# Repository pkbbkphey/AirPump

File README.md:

# AirPump

# Tools
- [Chinese to GBK](https://www.tusucao.com/commons/gbk/)

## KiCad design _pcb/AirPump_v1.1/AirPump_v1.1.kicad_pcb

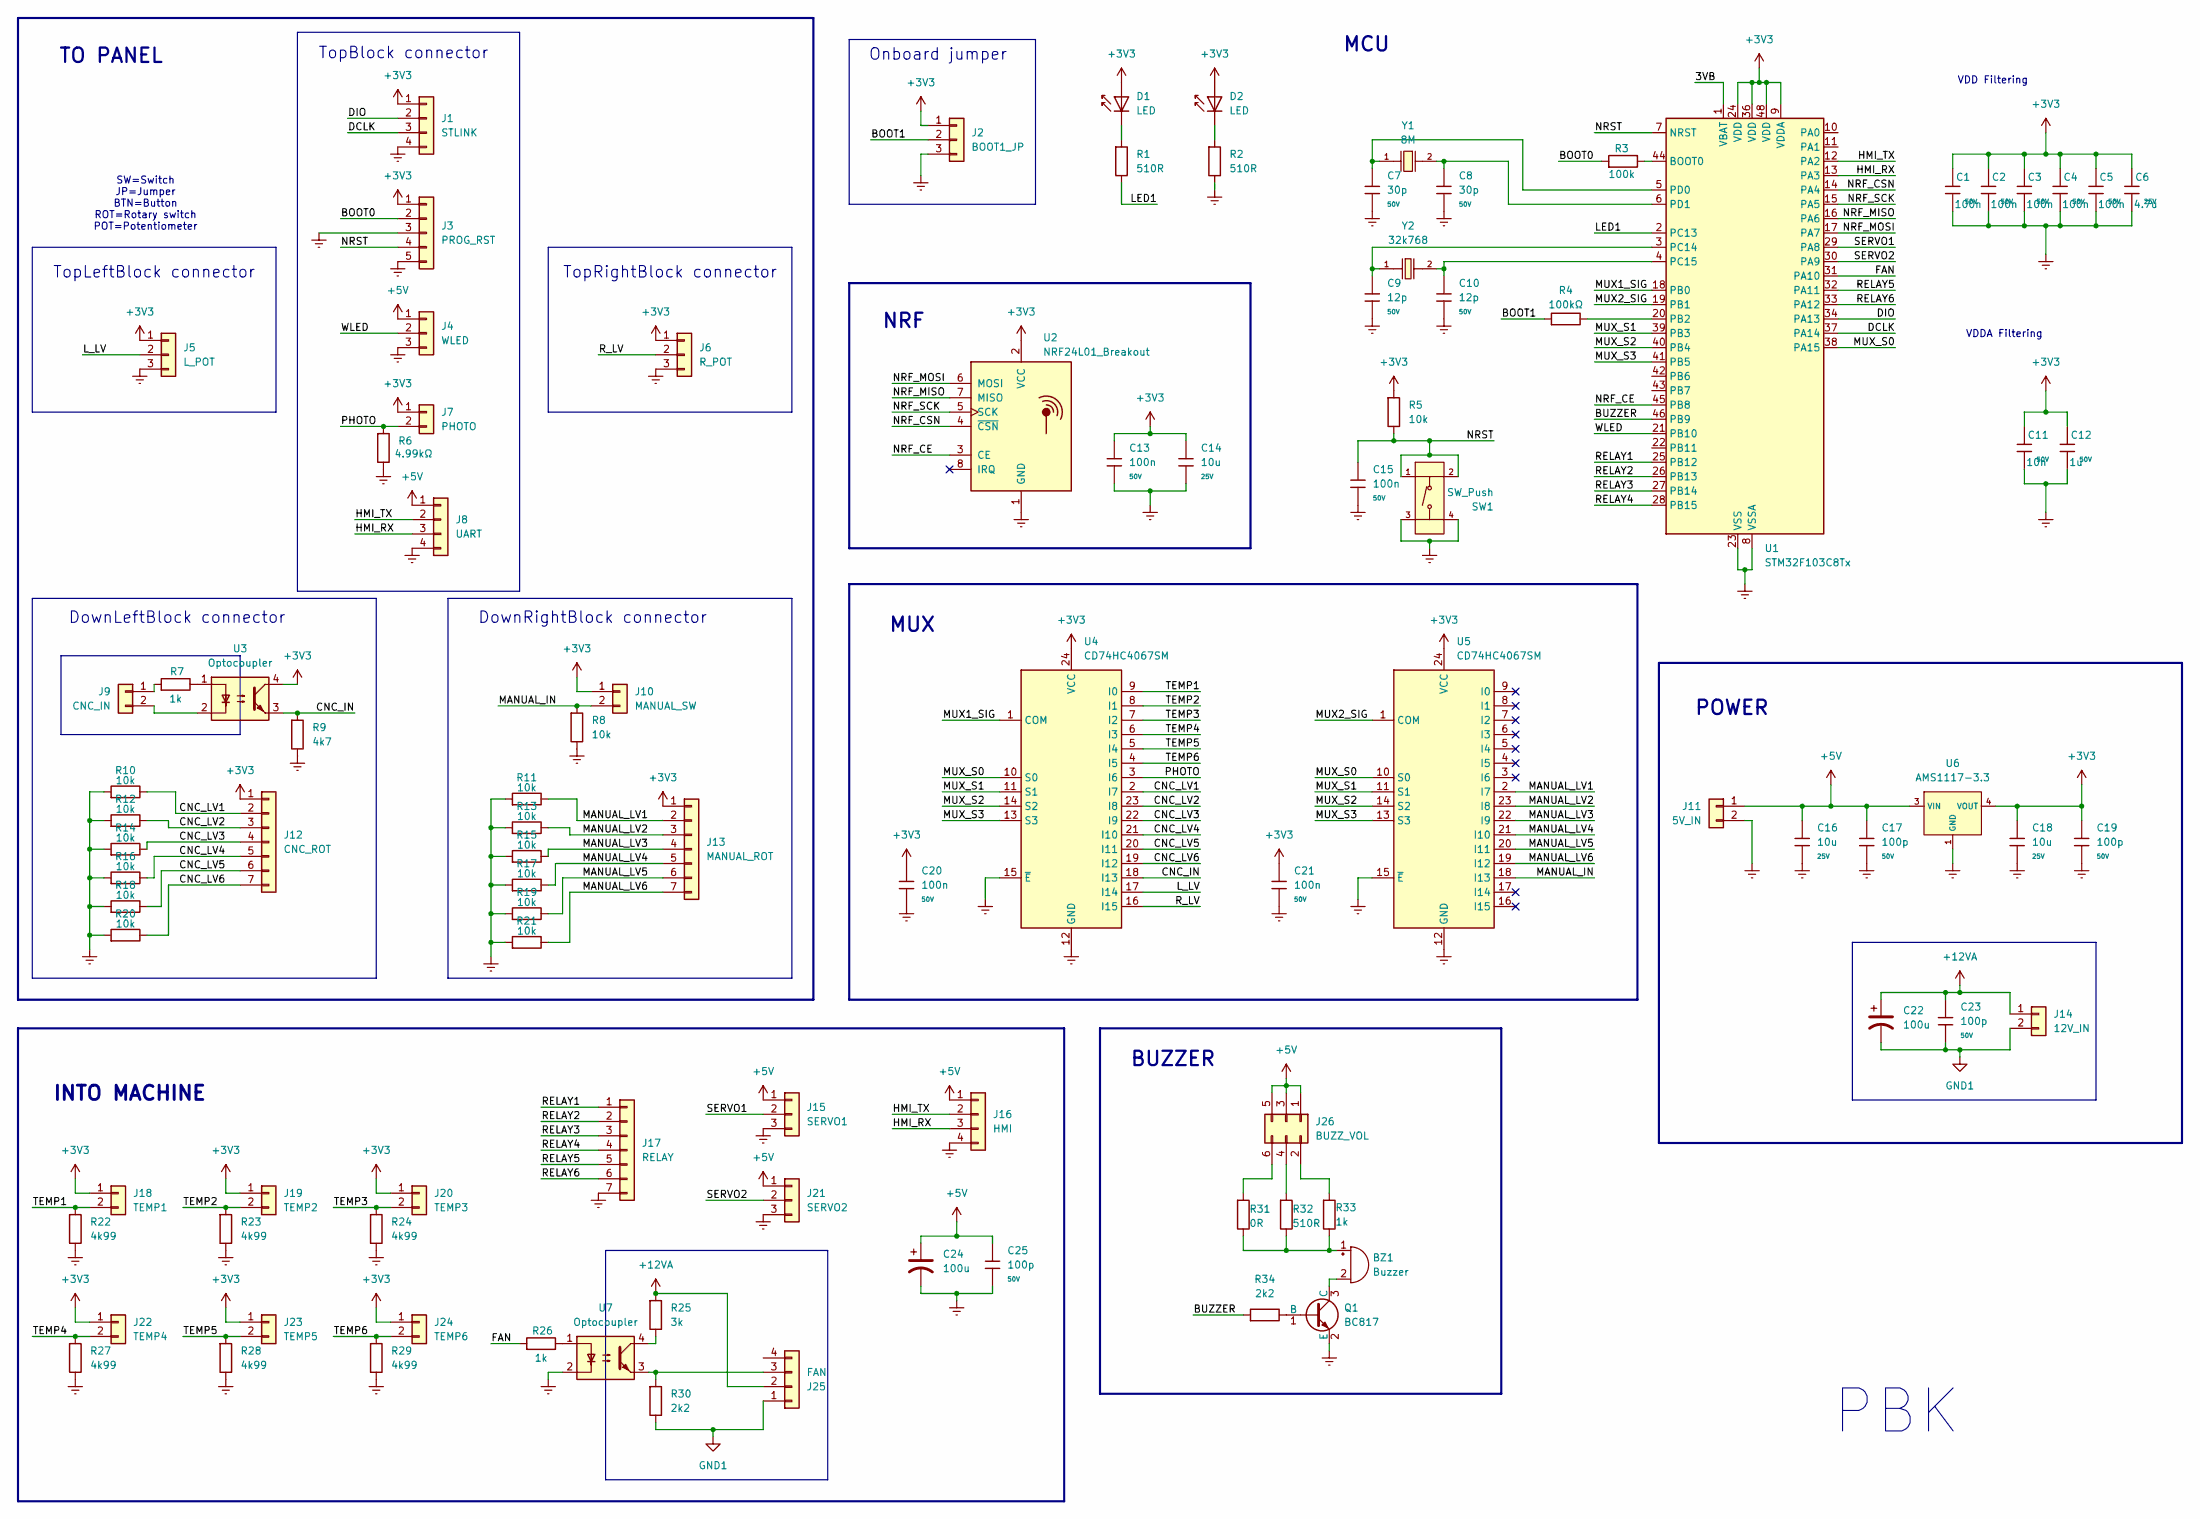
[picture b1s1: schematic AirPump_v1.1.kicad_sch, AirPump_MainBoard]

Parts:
BZ1: Buzzer; MagneticBuzzer_StarMicronics_QMX
C1, C2, C3, C4, C5, C13, C15, C20, C21: 100n; C_0603; Voltage Rated 50V; Tolerance ±10%; Part CC0603KRX7R9BB104; LCSC C14663
C6: 4.7u; C_0805; Voltage Rated 25V; Tolerance ±10%; Part CL21A475KAQNNNE; LCSC C1779
C7, C8: 30p; C_0603; Voltage Rated 50V; Tolerance ±5%; Part 0603CG300J500NT; LCSC C1658
C9, C10: 12p; C_0603; Voltage Rated 50V; Tolerance ±5%; Part CL10C120JB8NNNC; LCSC C38523
C11: 10n; C_0603; Voltage Rated 50V; Tolerance ±10%; Part 0603B103K500NT; LCSC C57112
C12: 1u; C_0603; Voltage Rated 50V; Tolerance ±10%; Part CL10A105KB8NNNC; LCSC C15849
C14, C16, C18: 10u; C_0805; Voltage Rated 25V; Tolerance ±10%; Part CL21A106KAYNNNE; LCSC C15850
C17, C19, C23, C25: 100p; C_0603; Voltage Rated 50V; Tolerance ±5%; Part CL10C101JB8NNNC; LCSC C14858
C22, C24: 100u; CP_Elec_6.3x5.4
D1: LED; D_0603; Part KT-0603W; LCSC C2290
D2: LED; D_0603; Part KT-0603R; LCSC C2286
J1: STLINK; JST_PH_B4B-PH-K_1x04_P2.00mm_Vertical
J2: BOOT1_JP; PinHeader_1x03_P2.54mm_Vertical
J3: PROG_RST; JST_PH_B5B-PH-K_1x05_P2.00mm_Vertical
J4: WLED; Molex_KK-254_AE-6410-03A_1x03_P2.54mm_Vertical
J5: L_POT; JST_PH_B3B-PH-K_1x03_P2.00mm_Vertical
J6: R_POT; JST_PH_B3B-PH-K_1x03_P2.00mm_Vertical
J7: PHOTO; JST_PH_B2B-PH-K_1x02_P2.00mm_Vertical
J8: UART; JST_PH_B4B-PH-K_1x04_P2.00mm_Vertical
J9: CNC_IN; JST_PH_B2B-PH-K_1x02_P2.00mm_Vertical
J10: MANUAL_SW; JST_PH_B2B-PH-K_1x02_P2.00mm_Vertical
J11: 5V_IN; Molex_KK-254_AE-6410-02A_1x02_P2.54mm_Vertical
J12: CNC_ROT; JST_PH_B7B-PH-K_1x07_P2.00mm_Vertical
J13: MANUAL_ROT; JST_PH_B7B-PH-K_1x07_P2.00mm_Vertical
J14: 12V_IN; Molex_KK-254_AE-6410-02A_1x02_P2.54mm_Vertical
J15: SERVO1; Molex_KK-254_AE-6410-03A_1x03_P2.54mm_Vertical
J16: HMI; Molex_KK-254_AE-6410-04A_1x04_P2.54mm_Vertical
J17: RELAY; JST_PH_B7B-PH-K_1x07_P2.00mm_Vertical
J18: TEMP1; JST_PH_B2B-PH-K_1x02_P2.00mm_Vertical
J19: TEMP2; JST_PH_B2B-PH-K_1x02_P2.00mm_Vertical
J20: TEMP3; JST_PH_B2B-PH-K_1x02_P2.00mm_Vertical
J21: SERVO2; Molex_KK-254_AE-6410-03A_1x03_P2.54mm_Vertical
J22: TEMP4; JST_PH_B2B-PH-K_1x02_P2.00mm_Vertical
J23: TEMP5; JST_PH_B2B-PH-K_1x02_P2.00mm_Vertical
J24: TEMP6; JST_PH_B2B-PH-K_1x02_P2.00mm_Vertical
J25: FAN; Molex_KK-254_AE-6410-04A_1x04_P2.54mm_Vertical
J26: BUZZ_VOL; PinHeader_2x03_P2.54mm_Vertical
Q1: BC817; Q_SOT-23; Part BC817-25; LCSC C20069154
R1, R2, R32: 510R; R_0603; Overload Voltage (Max) 75V; Tolerance ±1%; Part 0603WAF5100T5E; LCSC C23193
R3, R4: 100k; R_0603; Overload Voltage (Max) 75V; Tolerance ±1%; Part 0603WAF1003T5E; LCSC C25803
R5, R8, R10, R11, R12, R13, R14, R15, R16, R17, R18, R19, R20, R21: 10k; R_0603; Overload Voltage (Max) 75V; Tolerance ±1%; Part 0603WAF1002T5E; LCSC C25804
R6, R22, R23, R24, R27, R28, R29: 4k99; R_0603; Overload Voltage (Max) 75V; Tolerance ±1%; Part 0603WAF4991T5E; LCSC C23046
R7, R26, R33: 1k; R_0603; Overload Voltage (Max) 75V; Tolerance ±1%; Part 0603WAF1001T5E; LCSC C21190
R9: 4k7; R_0603; Overload Voltage (Max) 75V; Tolerance ±1%; Part 0603WAF4701T5E; LCSC C23162
R25: 3k; R_0603; Overload Voltage (Max) 75V; Tolerance ±1%; Part 0603WAF3001T5E; LCSC C4211
R30, R34: 2k2; R_0603; Overload Voltage (Max) 75V; Tolerance ±1%; Part 0603WAF2201T5E; LCSC C4190
R31: 0R; R_0603; Overload Voltage (Max) 75V; Tolerance ±1%; Part 0603WAF0000T5E; LCSC C21189
SW1: SW_Push; SW-SMD_4P-L5.1-W5.1-P3.70-LS6.5-TL-2; Voltage Rating (Dc) 12V; Part TS-1187A-B-A-B; LCSC C318884
U1: STM32F103C8Tx; LQFP-48_7x7mm_P0.5mm; Operating Voltage Range 2V~3.6V; Low Voltage Detection T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 2V~3.6V; Part STM32F103C8T6; LCSC C8734
U2: NRF24L01_Breakout; nRF24L01_Breakout
U3, U7: Optocoupler; SOP-4_3.8x4.1mm_P2.54mm; Part ICPL-356-50CEAXW; LCSC C42432283
U4, U5: CD74HC4067SM; SSOP-24_5.3x8.2mm_P0.65mm
U6: AMS1117-3.3; SOT-223-3_L6.5-W3.4-P2.30-LS7.0-BR; Output Voltage 3.3V; Dropout Voltage 1.3V@(800mA); Part AMS1117-3.3; LCSC C6186
Y1: 8M; CRYSTAL-SMD_L5.0-W3.2; Frequency Tolerance ±10ppm; Part X50328MSB2GI; LCSC C115962
Y2: 32k768; FC-135R_L3.2-W1.5; Frequency Tolerance ±20ppm; Part Q13FC13500004; LCSC C32346

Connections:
+3V3: C1.1, C2.1, C3.1, C4.1, C5.1, C6.1, C11.1, C12.1, C13.1, C14.1, C18.1, C19.1, C20.1, C21.1, D1.2, D2.2, J1.1, J2.1, J3.1, J5.1, J6.1, J7.1, J10.1, J12.1, J13.1, J18.1, J19.1, J20.1, J22.1, J23.1, J24.1, R5.1, U1.9 (VDDA), U1.24 (VDD), U1.36 (VDD), U1.48 (VDD), U2.2 (VCC), U3.4, U4.24 (VCC), U5.24 (VCC), U6.2 (VOUT), U6.4 (VOUT)
+5V: C16.1, C17.1, C24.1, C25.1, J4.1, J8.1, J11.1, J15.1, J16.1, J21.1, J26.1, J26.3, J26.5, U6.3 (VIN)
+12VA: C22.1, C23.1, J14.1, J25.2, R25.1
/3VB: U1.1 (VBAT)
/BOOT0: J3.2, R3.1
/BOOT1: J2.2, R4.1
/BUZZER: R34.1, U1.46 (PB9)
/CNC_IN: R9.1, U3.3, U4.18 (I13)
/CNC_LV1: J12.2, R10.2, U4.2 (I7)
/CNC_LV2: J12.3, R12.2, U4.23 (I8)
/CNC_LV3: J12.4, R14.2, U4.22 (I9)
/CNC_LV4: J12.5, R16.2, U4.21 (I10)
/CNC_LV5: J12.6, R18.2, U4.20 (I11)
/CNC_LV6: J12.7, R20.2, U4.19 (I12)
/DCLK: J1.3, U1.37 (PA14)
/DIO: J1.2, U1.34 (PA13)
/FAN: R26.1, U1.31 (PA10)
/HMI_RX: J8.3, J16.3, U1.13 (PA3)
/HMI_TX: J8.2, J16.2, U1.12 (PA2)
/LED1: R1.2, U1.2 (PC13)
/L_LV: J5.2, U4.17 (I14)
/MANUAL_IN: J10.2, R8.1, U5.18 (I13)
/MANUAL_LV1: J13.2, R11.2, U5.2 (I7)
/MANUAL_LV2: J13.3, R13.2, U5.23 (I8)
/MANUAL_LV3: J13.4, R15.2, U5.22 (I9)
/MANUAL_LV4: J13.5, R17.2, U5.21 (I10)
/MANUAL_LV5: J13.6, R19.2, U5.20 (I11)
/MANUAL_LV6: J13.7, R21.2, U5.19 (I12)
/MUX1_SIG: U1.18 (PB0), U4.1 (COM)
/MUX2_SIG: U1.19 (PB1), U5.1 (COM)
/MUX_S0: U1.38 (PA15), U4.10 (S0), U5.10 (S0)
/MUX_S1: U1.39 (PB3), U4.11 (S1), U5.11 (S1)
/MUX_S2: U1.40 (PB4), U4.14 (S2), U5.14 (S2)
/MUX_S3: U1.41 (PB5), U4.13 (S3), U5.13 (S3)
/NRF_CE: U1.45 (PB8), U2.3 (CE)
/NRF_CSN: U1.14 (PA4), U2.4 (~CSN)
/NRF_MISO: U1.16 (PA6), U2.7 (MISO)
/NRF_MOSI: U1.17 (PA7), U2.6 (MOSI)
/NRF_SCK: U1.15 (PA5), U2.5 (SCK)
/NRST: C15.1, J3.4, R5.2, SW1.1 (A), SW1.2 (B), U1.7 (NRST)
/PHOTO: J7.2, R6.1, U4.3 (I6)
/RELAY1: J17.1, U1.25 (PB12)
/RELAY2: J17.2, U1.26 (PB13)
/RELAY3: J17.3, U1.27 (PB14)
/RELAY4: J17.4, U1.28 (PB15)
/RELAY5: J17.5, U1.32 (PA11)
/RELAY6: J17.6, U1.33 (PA12)
/R_LV: J6.2, U4.16 (I15)
/SERVO1: J15.2, U1.29 (PA8)
/SERVO2: J21.2, U1.30 (PA9)
/TEMP1: J18.2, R22.1, U4.9 (I0)
/TEMP2: J19.2, R23.1, U4.8 (I1)
/TEMP3: J20.2, R24.1, U4.7 (I2)
/TEMP4: J22.2, R27.1, U4.6 (I3)
/TEMP5: J23.2, R28.1, U4.5 (I4)
/TEMP6: J24.2, R29.1, U4.4 (I5)
/WLED: J4.2, U1.21 (PB10)
Earth: C1.2, C2.2, C3.2, C4.2, C5.2, C6.2, C7.2, C8.2, C9.2, C10.2, C11.2, C12.2, C13.2, C14.2, C15.2, C16.2, C17.2, C18.2, C19.2, C20.2, C21.2, C24.2, C25.2, J1.4, J2.3, J3.3, J3.5, J4.3, J5.3, J6.3, J8.4, J11.2, J15.3, J16.4, J17.7, J21.3, Q1.2 (E), R2.2, R6.2, R8.2, R9.2, R10.1, R11.1, R12.1, R13.1, R14.1, R15.1, R16.1, R17.1, R18.1, R19.1, R20.1, R21.1, R22.2, R23.2, R24.2, R27.2, R28.2, R29.2, SW1.3 (C), SW1.4 (D), U1.8 (VSSA), U1.23 (VSS), U1.35 (VSS), U1.47 (VSS), U2.1 (GND), U4.12 (GND), U4.15 (~E), U5.12 (GND), U5.15 (~E), U6.1 (GND), U7.2
GND1: C22.2, C23.2, J14.2, J25.1, R30.2
unnamed: BZ1.1 (+), R31.2, R32.2, R33.2
unnamed: BZ1.2 (-), Q1.3 (C)
unnamed: D1.1, R1.1
unnamed: D2.1, R2.1
unnamed: J9.1, R7.1
unnamed: J9.2, U3.2
unnamed: J25.3, R30.1, U7.3
unnamed: J26.2, R33.1
unnamed: J26.4, R32.1
unnamed: J26.6, R31.1
unnamed: Q1.1 (B), R34.2
unnamed: R7.2, U3.1
unnamed: R25.2, U7.4
unnamed: R26.2, U7.1
unnamed: R3.2, U1.44 (BOOT0)
unnamed: R4.2, U1.20 (PB2)
unnamed: C9.1, U1.3 (PC14), Y2.1
unnamed: C10.1, U1.4 (PC15), Y2.2
unnamed: C7.1, U1.5 (PD0), Y1.1
unnamed: C8.1, U1.6 (PD1), Y1.2

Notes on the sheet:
POWER
DownLeftBlock connector
PBK
VDD Filtering
BUZZER
Onboard jumper
DownRightBlock connector
TopBlock connector
NRF
VDDA Filtering
TopRightBlock connector
TopLeftBlock connector
INTO MACHINE
MUX
TO PANEL
MCU
SW=Switch JP=Jumper BTN=Button ROT=Rotary switch POT=Potentiometer

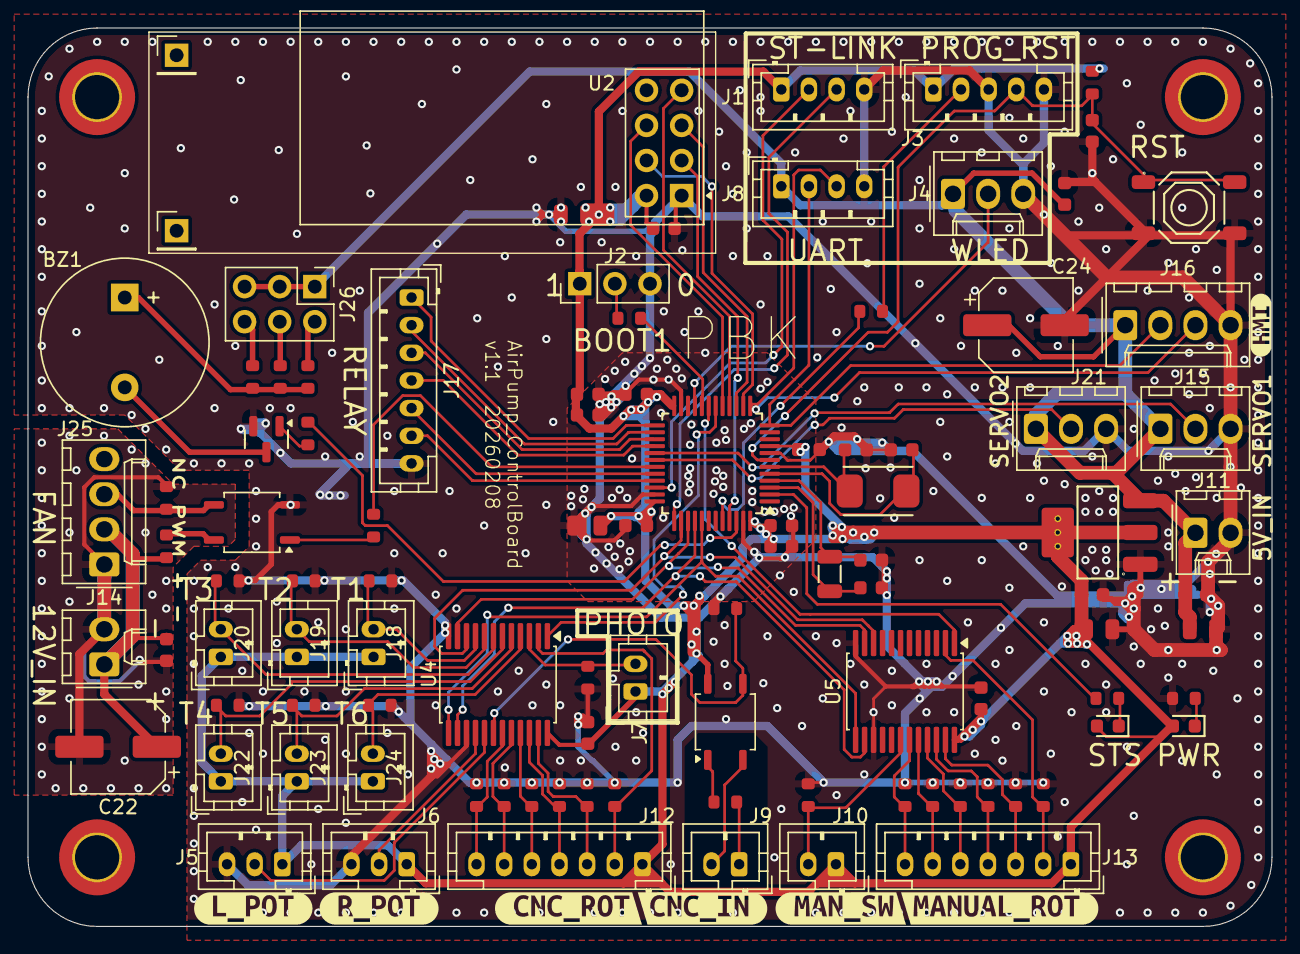
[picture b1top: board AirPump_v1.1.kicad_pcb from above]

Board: 2 copper layers, 90.0 x 65.0 mm, 106 parts (0 on the bottom side), 78 nets.

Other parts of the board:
kibuzzard-698717BE: G***; kibuzzard-698717BE
kibuzzard-698717CB: G***; kibuzzard-698717CB
kibuzzard-6987188B: G***; kibuzzard-6987188B
kibuzzard-6987189E: G***; kibuzzard-6987189E
kibuzzard-69871800: G***; kibuzzard-69871800
kibuzzard-69871850: G***; kibuzzard-69871850
kibuzzard-69871915: G***; kibuzzard-69871915

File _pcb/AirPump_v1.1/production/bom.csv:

Designator,Footprint,Quantity,Value,LCSC Part #
"C1, C13, C15, C2, C20, C21, C3, C4, C5",C_0603,9,100n,C14663
"C10, C9",C_0603,2,12p,C38523
C11,C_0603,1,10n,C57112
C12,C_0603,1,1u,C15849
"C14, C16, C18",C_0805,3,10u,C15850
"C17, C19, C23, C25",C_0603,4,100p,C14858
C6,C_0805,1,4.7u,C1779
"C7, C8",C_0603,2,30p,C1658
D1,D_0603,1,LED,C2290
D2,D_0603,1,LED,C2286
Q1,Q_SOT-23,1,BC817,C20069154
"R1, R2, R32",R_0603,3,510R,C23193
"R10, R11, R12, R13, R14, R15, R16, R17, R18, R19, R20, R21, R5, R8",R_0603,14,10k,C25804
"R22, R23, R24, R27, R28, R29, R6",R_0603,7,4k99,C23046
R25,R_0603,1,3k,C4211
"R26, R33, R7",R_0603,3,1k,C21190
"R3, R4",R_0603,2,100k,C25803
"R30, R34",R_0603,2,2k2,C4190
R31,R_0603,1,0R,C21189
R9,R_0603,1,4k7,C23162
SW1,SW-SMD_4P-L5.1-W5.1-P3.70-LS6.5-TL-2,1,SW_Push,C318884
U1,LQFP-48_7x7mm_P0.5mm,1,STM32F103C8Tx,C8734
"U3, U7",SOP-4_3.8x4.1mm_P2.54mm,2,Optocoupler,C42432283
"U4, U5",SSOP-24_5.3x8.2mm_P0.65mm,2,CD74HC4067SM,C98457
U6,SOT-223-3_L6.5-W3.4-P2.30-LS7.0-BR,1,AMS1117-3.3,C6186
Y1,CRYSTAL-SMD_L5.0-W3.2,1,8M,C115962
Y2,FC-135R_L3.2-W1.5,1,32k768,C32346

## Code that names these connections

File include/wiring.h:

#ifndef __WIRING_H__
#define __WIRING_H__
#include <Arduino.h>

// =================   Wiring   ================
constexpr int PIN_PumpRelay1 = PB12;
constexpr int PIN_PumpRelay2 = PB13;
constexpr int PIN_PumpRelay3 = PB14;
constexpr int PIN_PumpRelay4 = PB15;
constexpr int PIN_PumpRelay5 = PA11;
constexpr int PIN_PumpRelay6 = PA12;

constexpr int PIN_Servo1 = PA8;
constexpr int PIN_Servo2 = PA9;
constexpr int PIN_FanPWM = PA10;

constexpr int PIN_MUX_S0 = PA15;
constexpr int PIN_MUX_S1 = PB3;
constexpr int PIN_MUX_S2 = PB4;
constexpr int PIN_MUX_S3 = PB5;
constexpr int PIN_MUX1_SIG = PB0; // ADC
constexpr int PIN_MUX2_SIG = PB1; // ADC
/*
 *	MUX1 Channel Mapping:
 *	Channel  Signal
 *	=======  ======
 *	 0 ~ 5	 Pump Temperature Sensors 1 to 6
 *	 6		 Ambient Light Sensor
 *	 7 ~ 12  CNC Input Signal Level (Rotary Switch)
 *	 13      CNC Input (Optalcoupler)
 *   14      L Input Signal Level (Potentiometer)
 *   15      R Input Signal Level (Potentiometer)
 * 
 *  MUX2 Channel Mapping:
 *  Channel  Signal
 *  =======  ======
 *   7 ~ 12  Manual Input Signal Level (Rotary Switch)
 *   13      Manual Input (Switch)
 */

constexpr int PIN_BUZZER = PB9; // Timer
constexpr int PIN_WLED = PB10;	// Timer, 5V Tolerant
constexpr int PIN_LED = PC13;	// Onboard Status LED

/*
 *	Other Pins Used:
 *	Pin		Function
 *	===		========
 *  PA2	    Serial TX (to HMI)
 *  PA3	    Serial RX (from HMI)
 *  PA4	    nRF24L01 CSN
 *  PA5	    nRF24L01 SCK
 *  PB6     nRF24L01 MISO
 *  PB7     nRF24L01 MOSI
 *  R       Reset Button
 *  ST-link ST-link Programmer
 *  BOOT0   Boot0 Switch
 */
// ===========================================

#endif

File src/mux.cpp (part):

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double mux1_raw = 0, mux2_raw = 0;
int mux1_cnt = 0, mux2_cnt = 0;
void Mux::update(Out &out, Sys &sys) {
	mux1_raw += analogRead(PIN_MUX1_SIG);
	mux1_cnt++;
	mux2_raw += analogRead(PIN_MUX2_SIG);
	mux2_cnt++;

	// ==============================================================
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	}
	
    mux_channel_counter = (mux_channel_counter + 1) % 16;
    digitalWrite(PIN_MUX_S0, (mux_channel_counter >> 0) & 0x01);
    digitalWrite(PIN_MUX_S1, (mux_channel_counter >> 1) & 0x01);
    digitalWrite(PIN_MUX_S2, (mux_channel_counter >> 2) & 0x01);
    digitalWrite(PIN_MUX_S3, (mux_channel_counter >> 3) & 0x01);

	mux1_raw = 0;
	mux2_raw = 0;
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// 		return;
// 	last_mux_update_time = millis();
// 	// MUX1 update
// 	// Serial.print(analogRead(PIN_MUX1_SIG));
// 	// Serial.print(" ");
// 	// if(mux_channel_counter == 15) Serial.print("\n");

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//         case 0 ... 5:
//         {
//             // Pump Temperature Sensors 1 to 6
//             float temperature = analogRead(PIN_MUX1_SIG) * (3.3 / 4095.0) * 100.0 - 15.0;
//             out.pump.temperature[mux_channel_counter] = static_cast<int>(temperature);
// 			if(mux_channel_counter == 5)
// 			{
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// 		{
//             // Ambient Light Sensor
// 			float backlight_autobrightness_new = 
// 				analogRead(PIN_MUX1_SIG) * 0.6 * (1-out.setting.backlight_autobrightness_rate) +
// 				out.setting.backlight_autobrightness_r * out.setting.backlight_autobrightness_rate;
// 			out.setting.backlight_autobrightness_r = backlight_autobrightness_new;

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//         case 7 ... 12:
// 		{
//             // CNC Input Signal Level (Rotary Switch)
// 			bool cnc_in = (analogRead(PIN_MUX1_SIG) > 512);
// 			if(cnc_in)
// 				out.input_signal.cnc_rotary_switch_state |= (1 << (mux_channel_counter - 7));
// 			else
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//         case 13:
// 		{
//             // CNC Input (Optalcoupler)
// 			bool cnc_in = (analogRead(PIN_MUX1_SIG) > 512);
// 			if(cnc_in)
// 				out.input_signal.state |= 0b0010;
// 			else
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//         case 14:
// 		{
//             // L Input Signal Level (Potentiometer)
// 			int l_level = map(analogRead(PIN_MUX1_SIG), 0, 1023, 0, 100);
// 			out.input_signal.level[0] = constrain(l_level, 0, 100);
// 			if(l_level < 10)
// 				out.input_signal.state &= ~0b0001;
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//         case 15:
// 		{
//             // R Input Signal Level (Potentiometer)
// 			int r_level = map(analogRead(PIN_MUX1_SIG), 0, 1023, 0, 100);
// 			out.input_signal.level[2] = constrain(r_level, 0, 100);
// 			if(r_level < 10)
// 				out.input_signal.state &= ~0b00100;
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//         case 7 ... 12:
// 		{
//             // MANUAL Input Signal Level (Rotary Switch)
// 			bool manual_in = (analogRead(PIN_MUX2_SIG) > 512);
// 			if(manual_in)
// 				out.input_signal.manual_rotary_switch_state |= (1 << (mux_channel_counter - 7));
// 			else
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//         case 13:
// 		{
//             // MANUAL Input (Switch)
// 			bool manual_in = (analogRead(PIN_MUX2_SIG) > 512);
// 			if(manual_in)
// 				out.input_signal.state |= 0b10000;
// 			else
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// 	}
	
//     mux_channel_counter = (mux_channel_counter + 1) % 16;
//     digitalWrite(PIN_MUX_S0, (mux_channel_counter >> 0) & 0x01);
//     digitalWrite(PIN_MUX_S1, (mux_channel_counter >> 1) & 0x01);
//     digitalWrite(PIN_MUX_S2, (mux_channel_counter >> 2) & 0x01);
//     digitalWrite(PIN_MUX_S3, (mux_channel_counter >> 3) & 0x01);
// }

void Mux::debug()
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	return;
	last_mux_update_time = millis();

	Serial.print(analogRead(PIN_MUX1_SIG));
	Serial.print("\t");
	if(mux_channel_counter == 15) Serial.print("\n");

	mux_channel_counter = (mux_channel_counter + 1) % 16;
    digitalWrite(PIN_MUX_S0, (mux_channel_counter >> 0) & 0x01);
    digitalWrite(PIN_MUX_S1, (mux_channel_counter >> 1) & 0x01);
    digitalWrite(PIN_MUX_S2, (mux_channel_counter >> 2) & 0x01);
    digitalWrite(PIN_MUX_S3, (mux_channel_counter >> 3) & 0x01);
}
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
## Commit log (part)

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2026-01-28 PIO initialize
2026-01-30 Add communication protocol & Related Variables, Switch MCU to STM32
2026-02-01 Add wiring
2026-02-24 Add MUX Update
2026-02-28 Add hmi serial parser, hmi_update() status page
2026-03-01 Add manual part of UI, switch encoding to GBK
2026-03-01 Finish HMI interface v1.1
2026-03-01 UI and 3D model files backup
2026-03-01 PCB files backup
2026-03-01 Add AirPump image
2026-03-01 Update README
    Added an image for AirPump and updated the tools section.
2026-03-01 Utility backup
2026-03-04 Seperate hmi.cpp
2026-03-05 Fix MUX CNC_IN mistrigger
2026-03-05 Seperate mux.cpp, OOP
